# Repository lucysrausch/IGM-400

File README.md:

# IGM-400

Compiles with STM32duino on Linux.

Libraries used:
https://github.com/KenjutsuGH/Adafruit-ST7735-Library
https://github.com/adafruit/Adafruit-GFX-Library

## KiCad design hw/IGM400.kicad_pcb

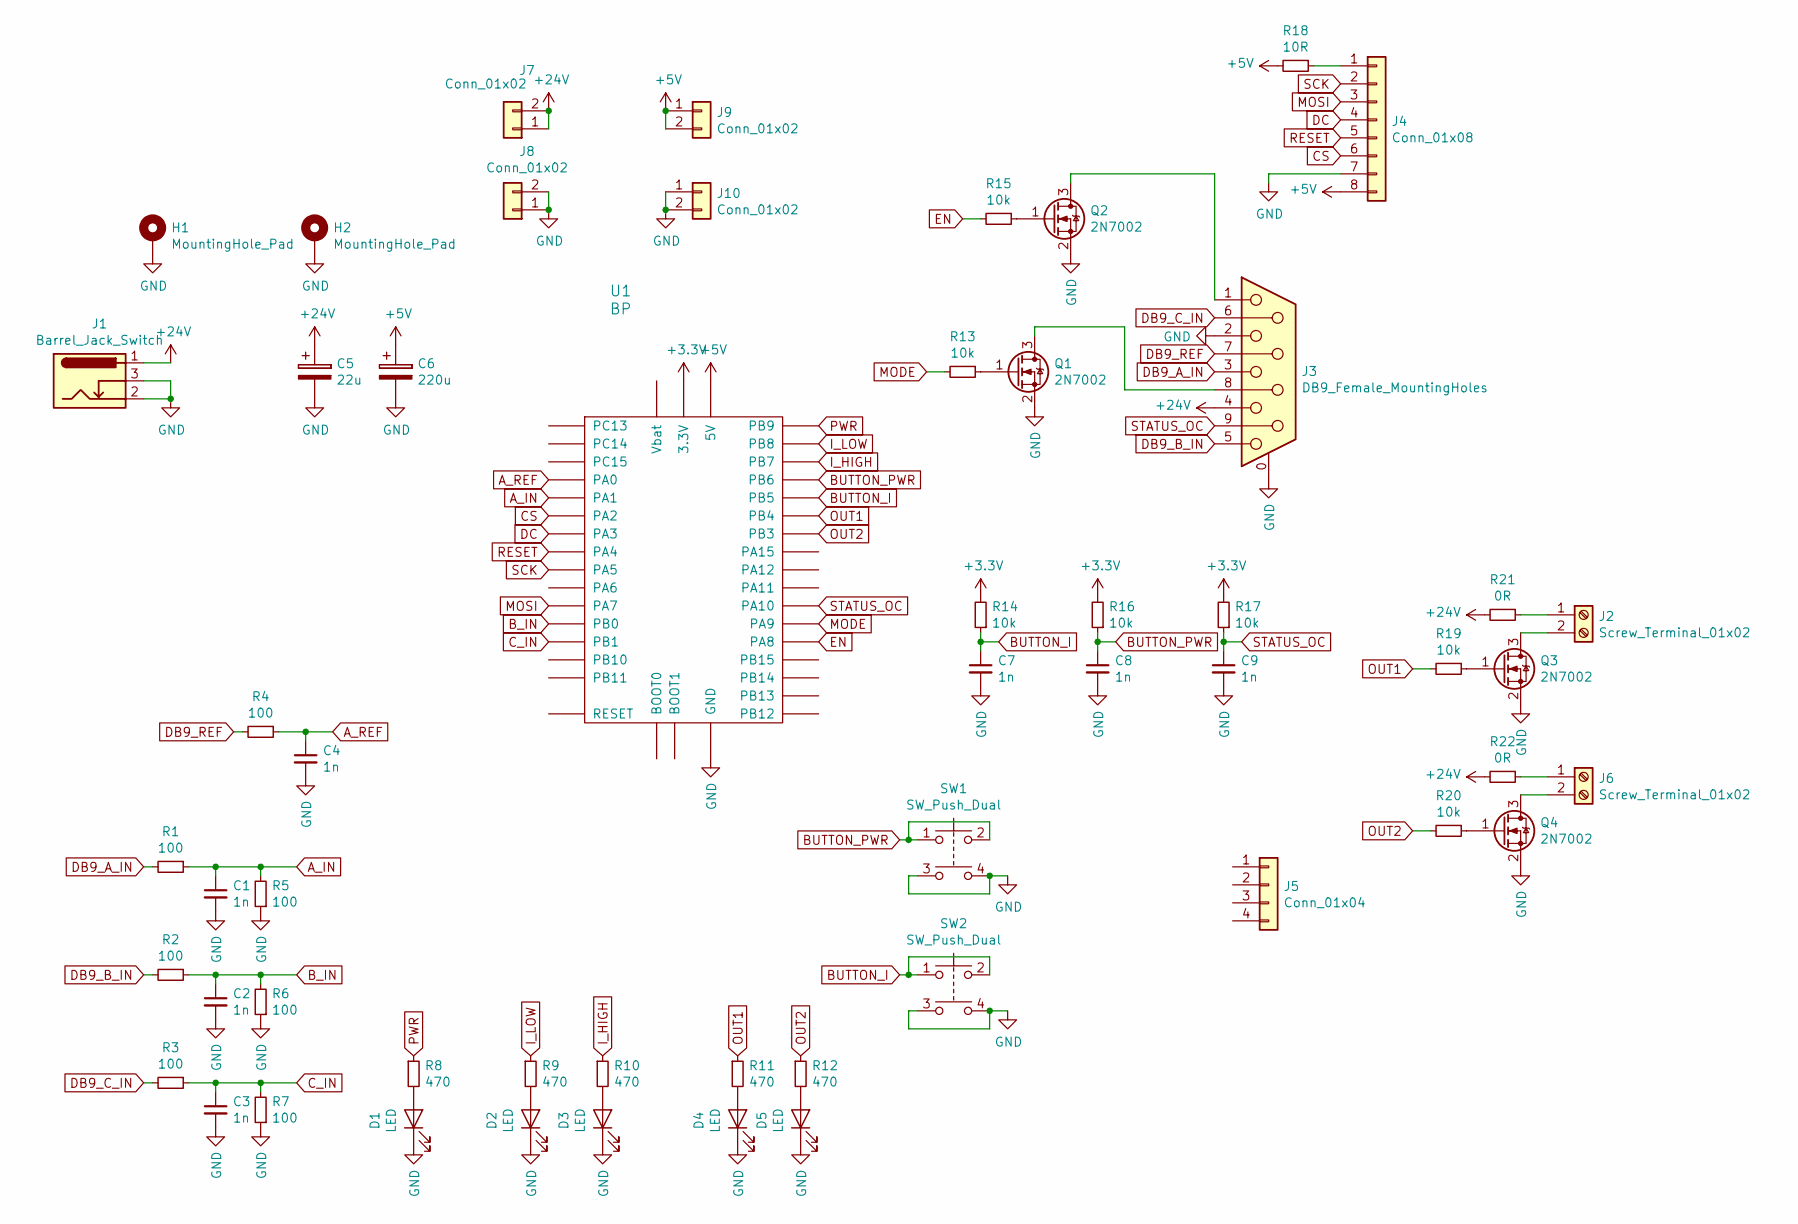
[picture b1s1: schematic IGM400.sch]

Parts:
C1, C2, C3, C4, C7, C8, C9: 1n; C_0603_1608Metric
C5: 22u; CP_Radial_D5.0mm_P2.50mm
C6: 220u; CP_Radial_D5.0mm_P2.50mm
D1, D2, D3, D4, D5: LED; LED_D3.0mm
H1, H2: MountingHole_Pad; MountingHole_3.2mm_M3_Pad_Via
J1: Barrel_Jack_Switch; BarrelJack_CUI_PJ-063AH_Horizontal
J2, J6: Screw_Terminal_01x02; TerminalBlock_bornier-2_P5.08mm
J3: DB9_Female_MountingHoles; DSUB-9_Female_Horizontal_P2.77x2.84mm_EdgePinOffset7.70mm_H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
J4: Conn_01x08; PinSocket_1x08_P2.54mm_Vertical
J5: Conn_01x04; PinSocket_1x04_P2.54mm_Vertical
J7, J8, J9, J10: Conn_01x02; PinSocket_1x02_P2.54mm_Vertical
Q1, Q2, Q3, Q4: 2N7002; SOT-23
R1, R2, R3, R4, R5, R6, R7: 100; R_0603_1608Metric
R8, R9, R10, R11, R12: 470; R_0603_1608Metric
R13, R14, R15, R16, R17, R19, R20: 10k; R_0603_1608Metric
R18: 10R; R_0603_1608Metric
R21, R22: 0R; R_0805_2012Metric
SW1, SW2: SW_Push_Dual; SW_TH_Tactile_Omron_B3F-10xx
U1: BP; BLUEPILL

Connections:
+3V3: R14.2, R16.2, R17.2, U1.3V3 (3.3V)
+5V: C6.1, J4.8, J9.1, J9.2, R18.2, U1.5V
+24V: C5.1, J1.1, J3.4, J7.1, J7.2, R21.2, R22.2
A_IN: C1.1, R1.1, R5.2, U1.PA1
A_REF: C4.1, R4.1, U1.PA0
BUTTON_I: C7.1, R14.1, SW2.1, SW2.2, U1.PB5
BUTTON_PWR: C8.1, R16.1, SW1.1, SW1.2, U1.PB6
B_IN: C2.1, R2.1, R6.2, U1.PB0
CS: J4.6, U1.PA2
C_IN: C3.1, R3.1, R7.2, U1.PB1
DB9_A_IN: J3.3, R1.2
DB9_B_IN: J3.5, R2.2
DB9_C_IN: J3.6, R3.2
DB9_REF: J3.7, R4.2
DC: J4.4, U1.PA3
EN: R15.2, U1.PA8
GND: C1.2, C2.2, C3.2, C4.2, C5.2, C6.2, C7.2, C8.2, C9.2, D1.1 (K), D2.1 (K), D3.1 (K), D4.1 (K), D5.1 (K), H1.1, H2.1, J1.2, J1.3, J3.0 (PAD), J3.2, J4.7, J8.1, J8.2, J10.1, J10.2, Q1.2 (S), Q2.2 (S), Q3.2 (S), Q4.2 (S), R5.1, R6.1, R7.1, SW1.3, SW1.4, SW2.3, SW2.4, U1.G (GND)
I_HIGH: R10.1, U1.PB7
I_LOW: R9.1, U1.PB8
MODE: R13.2, U1.PA9
MOSI: J4.3, U1.PA7
unnamed: D1.2 (A), R8.2
unnamed: D2.2 (A), R9.2
unnamed: D3.2 (A), R10.2
unnamed: D4.2 (A), R11.2
unnamed: D5.2 (A), R12.2
unnamed: J2.1, R21.1
unnamed: J2.2, Q3.3 (D)
unnamed: J3.1, Q2.3 (D)
unnamed: J3.8, Q1.3 (D)
unnamed: J4.1, R18.1
unnamed: J6.1, R22.1
unnamed: J6.2, Q4.3 (D)
unnamed: Q1.1 (G), R13.1
unnamed: Q2.1 (G), R15.1
unnamed: Q3.1 (G), R19.1
unnamed: Q4.1 (G), R20.1
OUT1: R11.1, R19.2, U1.PB4
OUT2: R12.1, R20.2, U1.PB3
PWR: R8.1, U1.PB9
RESET: J4.5, U1.PA4
SCK: J4.2, U1.PA5
STATUS_OC: C9.1, J3.9, R17.1, U1.PA10

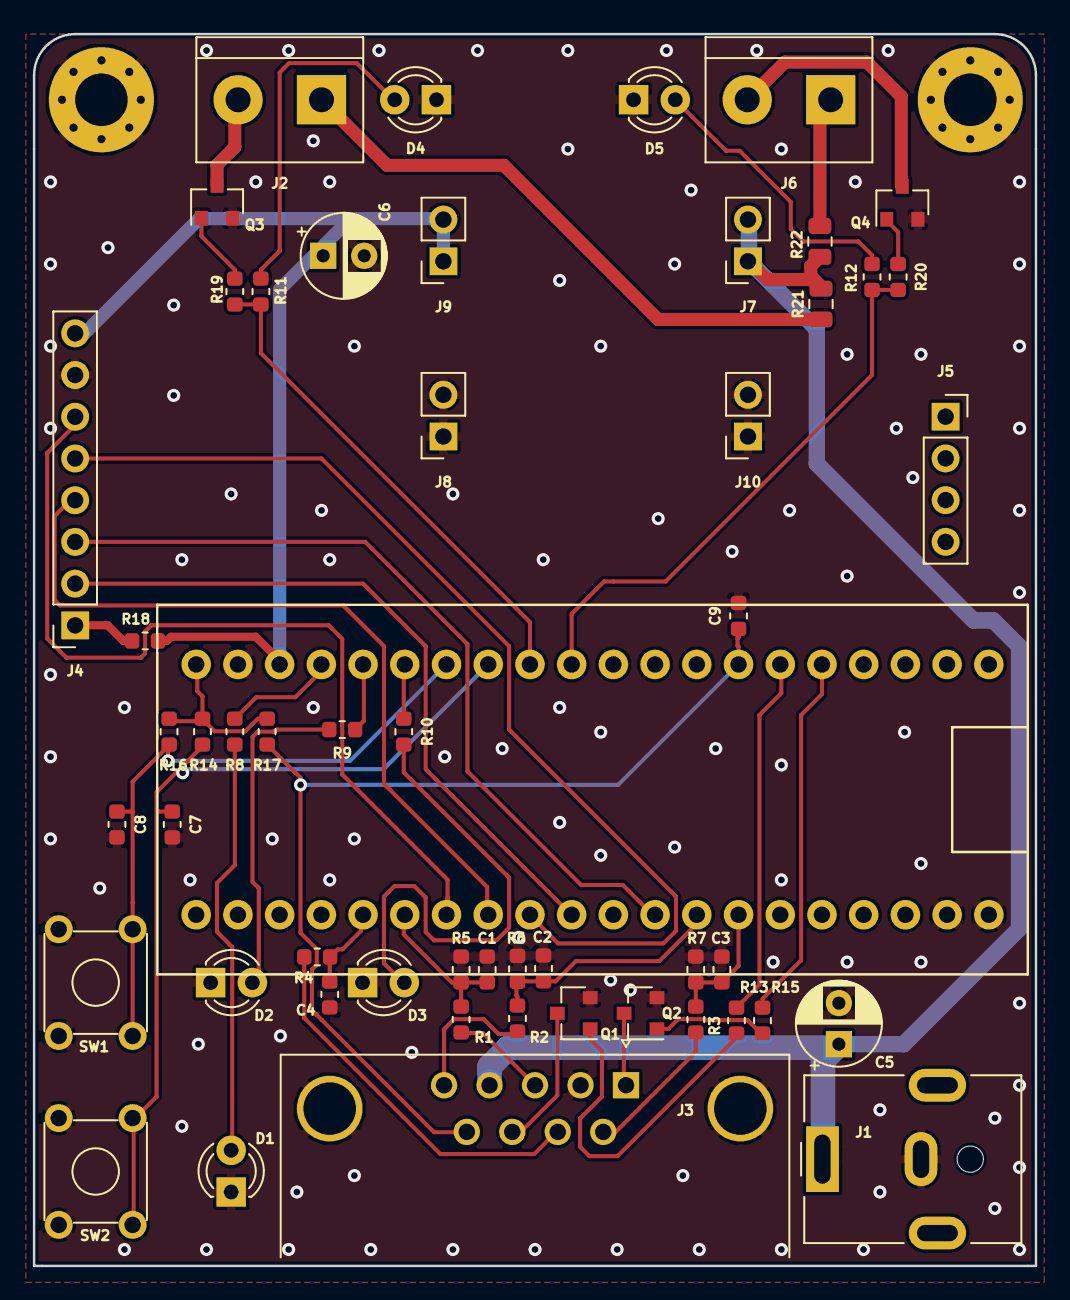
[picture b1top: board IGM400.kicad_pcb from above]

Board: 2 copper layers, 61.0 x 75.0 mm, 55 parts (0 on the bottom side), 43 nets.

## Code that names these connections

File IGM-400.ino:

#include <Adafruit_GFX.h>    // Core graphics library

#include "Adafruit_ST7735.h" // Hardware-specific library

#define TFT_CS     PA2
#define TFT_RST    PA4
#define TFT_DC     PA3

#include <Fonts/FreeSans24pt7b.h>
#include <Fonts/FreeSans18pt7b.h>
#include <Fonts/FreeSans12pt7b.h>
#include <Fonts/FreeSans9pt7b.h>

Adafruit_ST7735 tft = Adafruit_ST7735(TFT_CS,  TFT_DC, TFT_RST);

float pressure = 0;
float last_pressure = 0;
uint8_t exponent = 0;
uint8_t last_exponent = 0;
uint8_t stat = 0;

uint8_t pressure_history[136];
uint8_t color_history[136];

void setup(void) {
  pinMode(PA8, OUTPUT);
  pinMode(PA9, OUTPUT);

  pinMode(PB3, OUTPUT);
  pinMode(PB4, OUTPUT);
  pinMode(PB7, OUTPUT);
  pinMode(PB8, OUTPUT);
  pinMode(PB9, OUTPUT);

  digitalWrite(PA8, LOW);
  digitalWrite(PA9, LOW);

  digitalWrite(PB3, LOW);
  digitalWrite(PB4, LOW);
  digitalWrite(PB7, LOW);
  digitalWrite(PB8, LOW);
  digitalWrite(PB9, LOW);


  Serial.begin();
  Serial.print("Hello! ST7735 TFT Test");

  // Use this initializer if you're using a 1.8" TFT
  tft.initR(INITR_BLACKTAB);   // initialize a ST7735S chip, black tab

  tft.setRotation(3);
  tft.fillScreen(ST7735_BLACK);

  Serial.println("Initialized");

  tft.setCursor(35, 2);
  tft.setFont();
  tft.print("IGM-400 Display");
}

void updatePressure() {
  tft.setTextColor(ST7735_WHITE);

  if (last_pressure * 100 != pressure * 100) {
    tft.fillRect(7, 47, 90, 34, ST7735_BLACK);
    last_pressure = pressure;
  }

  if (last_exponent != exponent) {
    tft.fillRect(122, 38, 20, 25, ST7735_BLACK);
    tft.fillRect(150, 89, 7, 34, ST7735_BLACK);
    last_exponent = exponent;
  }
  
  tft.setCursor(7, 73);
  tft.setFont(&FreeSans24pt7b);
  tft.print(pressure);

  tft.setCursor(97, 79);
  tft.setFont(&FreeSans9pt7b);
  tft.print("x10");

  tft.setCursor(112, 62);
  tft.setFont(&FreeSans18pt7b);
  tft.print("-");
  tft.print(exponent);

  tft.setCursor(130, 79);
  tft.setFont();
  tft.print("mbar");  
}

void updateGraph() {
  pressure_history[0] = pressure * 3.2;
  color_history[0] = (exponent * 25) + (pressure * 2.5);

  for (int i = sizeof(pressure_history); i > 0; i--) {
    tft.drawFastVLine(7+(137-i), 87 + (33 - pressure_history[i]), pressure_history[i], ST7735_BLACK);
    pressure_history[i] = pressure_history[i-1];
    color_history[i] = color_history[i-1];
    tft.drawFastVLine(7+(137-i), 87 + (33 - pressure_history[i-1]), pressure_history[i-1], ((color_history[i-1] & 0xF8) << 8) | (((255 - color_history[i-1]) & 0xFC) << 3));
  }

  tft.drawFastVLine(144, 89, 31, ST7735_WHITE);

  tft.drawFastHLine(146, 92, 3, ST7735_WHITE);
  tft.drawFastHLine(146, 114, 3, ST7735_WHITE);

  tft.drawFastHLine(8, 119, 137, ST7735_WHITE);

  tft.setTextColor(ST7735_WHITE);
  tft.setFont();
  tft.setCursor(150, 89);
  tft.print(exponent-1); 
  tft.setCursor(150, 111);
  tft.print((exponent)); 


  tft.setCursor(8, 121);
  tft.print("-10s");

  tft.setCursor(73, 121);
  tft.print("-5s");

  tft.setCursor(139, 121);
  tft.print("0s");
}

uint8_t powerbtn_state = 0;


void loop() {
  if (digitalRead(PB5) == LOW && powerbtn_state == 1) {
    stat = !stat;
    tft.fillRect(7, 24, 80, 12, ST7735_BLACK);
  }
  powerbtn_state = digitalRead(PB5);

  digitalWrite(PA8, (stat == 1));
  digitalWrite(PB9, (stat == 1));

  
  tft.setFont();
  tft.setTextColor(ST7735_WHITE);
  tft.setCursor(8, 15);
  tft.print("Status:");
  
  tft.setCursor(8, 25);
  if (stat == 1) {
    tft.setTextColor(ST7735_GREEN);
    tft.print("active");
  } else if (stat == 0) {
    tft.setTextColor(ST7735_RED);
    tft.print("off");  
  }

  tft.setTextColor(ST7735_WHITE);
  tft.setCursor(80, 15);
  tft.print("Mode:");
  tft.setCursor(80, 25);
  tft.setTextColor(ST7735_WHITE);
  tft.print("100uA");  
  
  updatePressure();
  updateGraph();

  // 3,115264798V = 10V
  // 3866 = 10V

  float analog = ((float)analogRead(PA1) / 3866.0f) - ((float)analogRead(PA0) / 12410.0f);
  exponent = 10 - (analog * 10.0f);

  for (int i = 0; i < 35; i++) {
    pressure = pressure * 0.99f + pow(10.0, (analog * 10.0) - (int)(analog * 10.0)) * 0.01f;
    delay(2);
  }

  if (exponent >= 10) {
    exponent = 9;
  }

  if (pressure >= 9.99) {
    pressure = 0;
  } 
}

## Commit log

2019-04-05 ADD: kicad and gerber files
